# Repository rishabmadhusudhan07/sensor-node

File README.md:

# ESP32 Low-Power Weather Node
A custom ESP32-based weather sensor node targeting six months of battery life and less than 50 µA system current during deep sleep. The project was motivated by gaps observed while mapping environmental data across the Pacific Northwest during a National Weather Service internship.

Planned firmware will use ESP-IDF and statically allocated FreeRTOS tasks for sensor sampling, local logging, wireless transmission, and deep-sleep control. Later revisions may add transmission integrity checks and adaptive sampling based on changing weather conditions.

Status: In development. The initial schematic and PCB layout are complete but not yet been assembled. BME280 I2C communication is being tested. Chip ID was verified. Compensated temperature/pressure/humidity values are in progress. Currently being tested on a XIAO ESP32-S3. [Project Status](#project-status).

---
 
## Why this project
 
A low-cost, low-power sensor node could make denser local observations more practical. This project explores the engineering requirements for that type of device.

## Hardware
The following values are estimates based on component datasheets and haven't been verified on assembled hardware.

| Component | Role | Sleep current |
|---|---|---|
| ESP32-WROOM-32E-N4 | MCU + WiFi | ~10 µA |
| BME280 (through-hole breakout, soldered on) | Temp / humidity / pressure, forced mode | ≥0.1 µA sensor only |
| BH1750FVI-TR (bare IC, reflowed) | Ambient light | 1 µA |
| TPB4056A20-DFGR | LiPo charge management | <2 µA |
| RT9080-33GJ5 | 3.3V LDO regulator, 600 mA max | ~2 µA |
 
Target: <50 µA average system sleep current.

## Design decisions
 
**ESP-IDF over Arduino.** ESP-IDF was selected to provide direct control over FreeRTOS task creation, static memory allocation, peripheral configuration, and ESP32 sleep/wake behavior.
 
**LDO instead of a buck-boost regulator.** An LDO offers a simpler design and lower quiescent current, though reduced usable battery voltage as the LiPo approaches the regulator’s dropout region. The RT9080-33GJ5 was selected for its ~2 µA quiescent current and 600 mA output rating. Did not use MCP1700 because of its 250 mA rating, which isn't enough for WiFi transmission.
 
**No onboard current-sense IC.** It needs to measure sleep current in the microamps as well as much larger Wi-Fi transmission currents. Instead of a dedicated IC, test points are placed across a removable jumper. The jumper can be replaced by a larger resistor for controlled sleep measurements or a lower one for active measurements. An INA219 did not provide sufficient dynamic range for both measurements with a single resistor, while the INA228 drew too much current.
 
**Adaptive sampling instead of a fixed interval.** The planned firmware will have a rolling window of pressure measurements, estimate the rate of change, and adjust the next sampling interval. Faster changes, such as a cold front or wind shift, will mean more frequent sampling; stable conditions mean longer sleep intervals.

**Fully static FreeRTOS allocation.** Every task and queue will be created statically to keep predictable memory usage.

## Repo structure
 
```
├── firmware/       # ESP-IDF project
├── hardware/       # KiCad schematic + PCB layout
└── README.md
```

## Project status
 
| Phase                                   | Status      |
| --------------------------------------- | ----------- |
| Rev A schematic and PCB layout          | Complete    |
| PCB fabrication and bring-up            | Complete    |
| Sensor firmware                         | In progress |
| FreeRTOS task implementation            | In Progress |
| Data integrity and Wi-Fi retry pipeline | Not started |
| Power characterization                  | Not started |
| Field testing                           | Not started |

## License
 
MIT — see [LICENSE](LICENSE).

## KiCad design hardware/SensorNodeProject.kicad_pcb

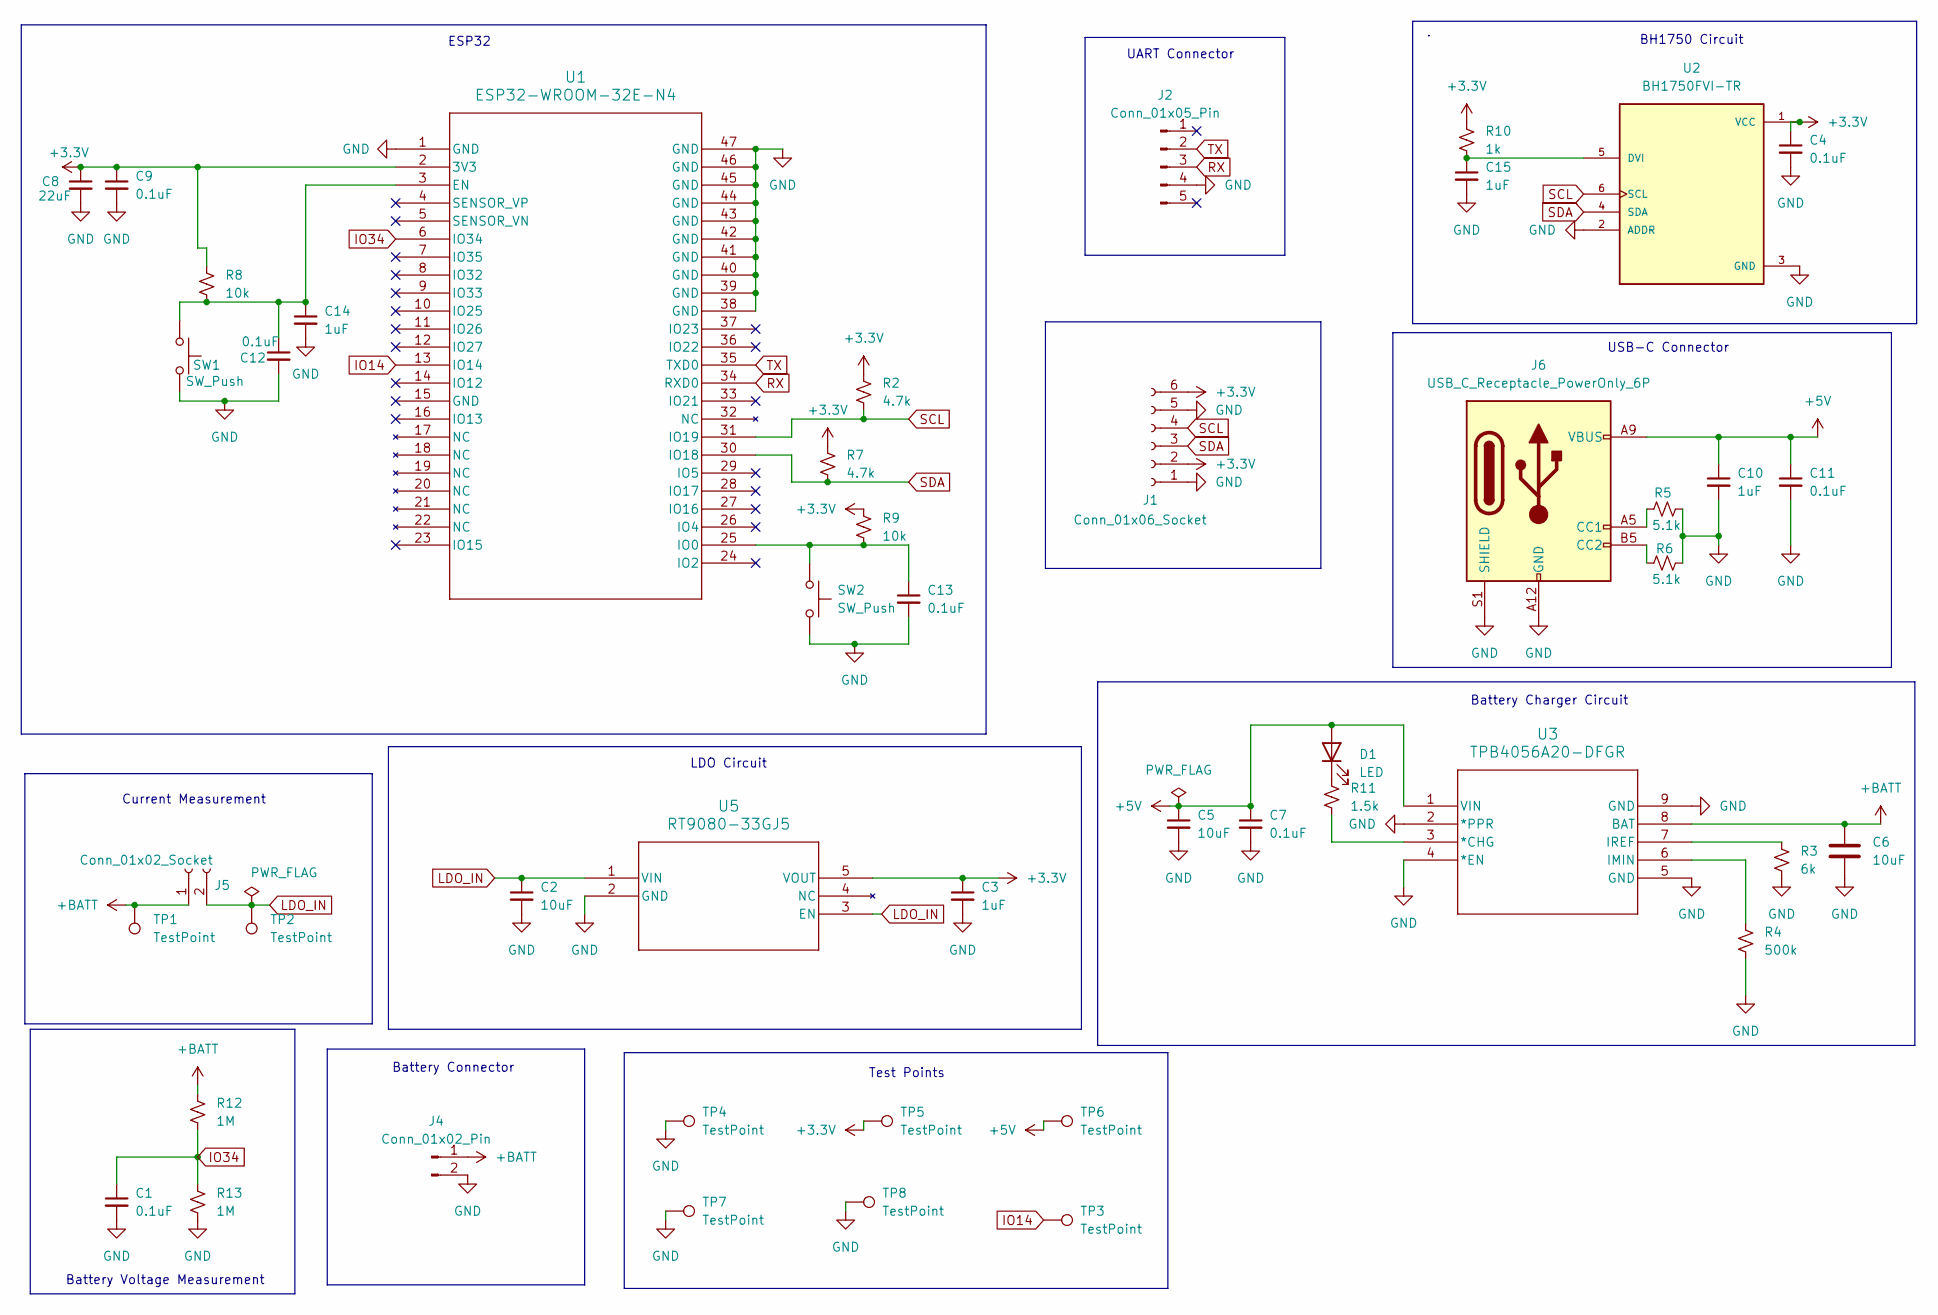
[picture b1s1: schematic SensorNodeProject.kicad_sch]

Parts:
C1, C4, C7, C9, C11, C12, C13: 0.1uF; C_0805_2012Metric_Pad1.18x1.45mm_HandSolder
C2, C5, C6: 10uF; C_0805_2012Metric_Pad1.18x1.45mm_HandSolder
C3, C10, C14, C15: 1uF; C_0805_2012Metric_Pad1.18x1.45mm_HandSolder
C8: 22uF; C_0805_2012Metric_Pad1.18x1.45mm_HandSolder
D1: LED; LED_1206_3216Metric_Pad1.42x1.75mm_HandSolder
J1: Conn_01x06_Socket; PinHeader_1x06_P2.54mm_Vertical
J2: Conn_01x05_Pin; PinHeader_1x05_P2.54mm_Vertical
J4: Conn_01x02_Pin; JST_PH_B2B-PH-K_1x02_P2.00mm_Vertical
J5: Conn_01x02_Socket; PinSocket_1x02_P2.54mm_Vertical
J6: USB_C_Receptacle_PowerOnly_6P; USB_C_Receptacle_GCT_USB4125-xx-x_6P_TopMnt_Horizontal
R2, R7: 4.7k; R_0805_2012Metric_Pad1.20x1.40mm_HandSolder
R3: 6k; R_0805_2012Metric_Pad1.20x1.40mm_HandSolder
R4: 500k; R_0805_2012Metric_Pad1.20x1.40mm_HandSolder
R5, R6: 5.1k; R_0805_2012Metric_Pad1.20x1.40mm_HandSolder
R8, R9: 10k; R_0805_2012Metric_Pad1.20x1.40mm_HandSolder
R10: 1k; R_0805_2012Metric_Pad1.20x1.40mm_HandSolder
R11: 1.5k; R_0805_2012Metric_Pad1.20x1.40mm_HandSolder
R12, R13: 1M; R_0805_2012Metric_Pad1.20x1.40mm_HandSolder
SW1, SW2: SW_Push; SW_TS04-66-50-BK-160-SMT
TP1, TP2, TP3, TP4, TP5, TP6, TP7, TP8: TestPoint; TestPoint_Loop_D2.50mm_Drill1.0mm
U1: ESP32-WROOM-32E-N4; ESP32­WROOM­32E_EXP
U2: BH1750FVI-TR; BH1750FVI-TR_ROM; PARTREV D
U3: TPB4056A20-DFGR; DFN2X2-8_TPK
U5: RT9080-33GJ5; TSOT-23-5_RIT

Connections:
+3.3V: C3.1, C4.1, C8.1, C9.1, J1.2, J1.6, R2.1, R7.1, R8.1, R9.1, R10.1, TP5.1, U1.2 (3V3), U2.1 (VCC), U5.5 (VOUT)
+5V: C5.1, C7.1, C10.1, C11.1, D1.2 (A), J6.A9 (VBUS), J6.B9 (VBUS), TP6.1, U3.1 (VIN)
+BATT: C6.1, J4.1, J5.1, R12.2, TP1.1, U3.8 (BAT)
GND: C1.2, C2.2, C3.2, C4.2, C5.2, C6.2, C7.2, C8.2, C9.2, C10.2, C11.2, C12.2, C13.2, C14.2, C15.2, J1.1, J1.5, J2.4, J4.2, J6.A12 (GND), J6.B12 (GND), J6.S1 (SHIELD), R3.2, R4.2, R5.2, R6.2, R13.1, SW1.2, SW2.2, TP4.1, TP7.1, TP8.1, U1.1 (GND), U1.38 (GND), U1.39 (GND), U1.40 (GND), U1.41 (GND), U1.42 (GND), U1.43 (GND), U1.44 (GND), U1.45 (GND), U1.46 (GND), U1.47 (GND), U2.2 (ADDR), U2.3 (GND), U3.2 (*PPR), U3.4 (*EN), U3.5 (GND), U3.9 (GND), U5.2 (GND)
IO14: TP3.1, U1.13 (IO14)
IO34: C1.1, R12.1, R13.2, U1.6 (IO34)
LDO_IN: C2.1, J5.2, TP2.1, U5.1 (VIN), U5.3 (EN)
unnamed: D1.1 (K), R11.1
unnamed: J6.A5 (CC1), R5.1
unnamed: J6.B5 (CC2), R6.1
unnamed: C12.1, C14.1, R8.2, SW1.1, U1.3 (EN)
unnamed: C13.1, R9.2, SW2.1, U1.25 (IO0)
unnamed: C15.1, R10.2, U2.5 (DVI)
unnamed: R11.2, U3.3 (*CHG)
unnamed: R4.1, U3.6 (IMIN)
unnamed: R3.1, U3.7 (IREF)
RX: J2.3, U1.34 (RXD0)
SCL: J1.4, R2.2, U1.31 (IO19), U2.6 (SCL)
SDA: J1.3, R7.2, U1.30 (IO18), U2.4 (SDA)
TX: J2.2, U1.35 (TXD0)

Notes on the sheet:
LDO Circuit
BH1750 Circuit
USB-C Connector
UART Connector
ESP32
Battery Charger Circuit
Current Measurement
Battery Voltage Measurement
Test Points
Battery Connector

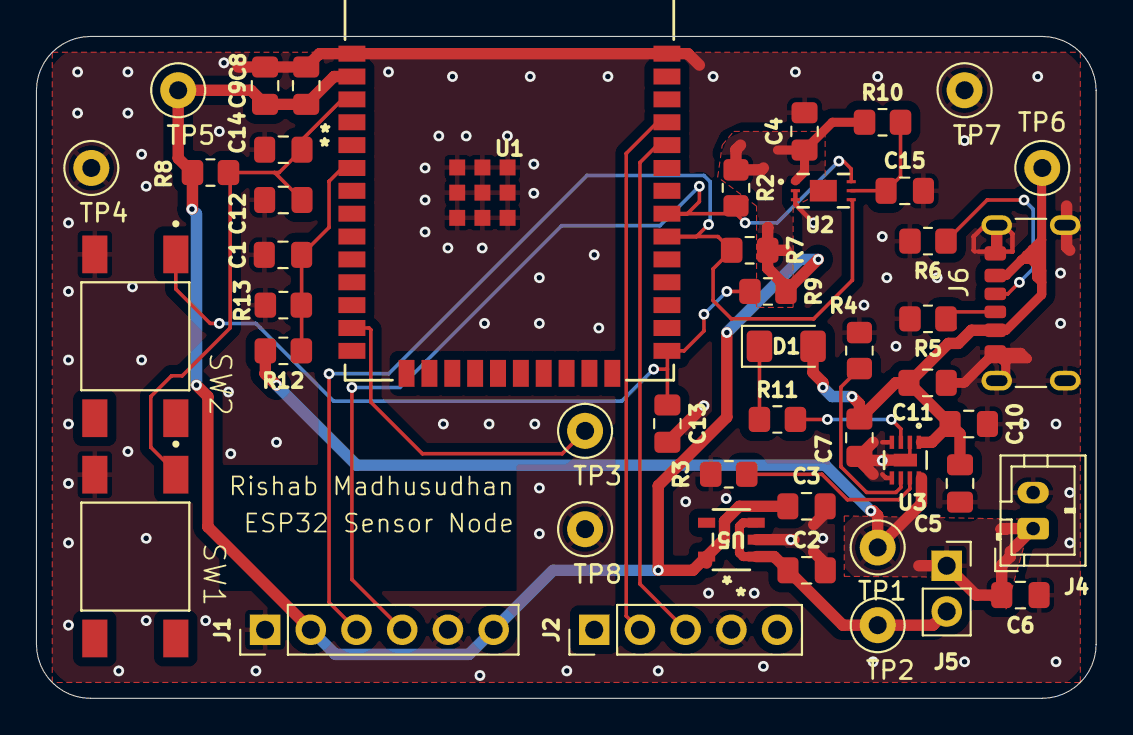
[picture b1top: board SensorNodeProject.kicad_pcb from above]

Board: 2 copper layers, 58.9 x 36.8 mm, 47 parts (0 on the bottom side), 20 nets.
